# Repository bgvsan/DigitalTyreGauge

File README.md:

# DigitalTyreGauge
Digital tyre gauge

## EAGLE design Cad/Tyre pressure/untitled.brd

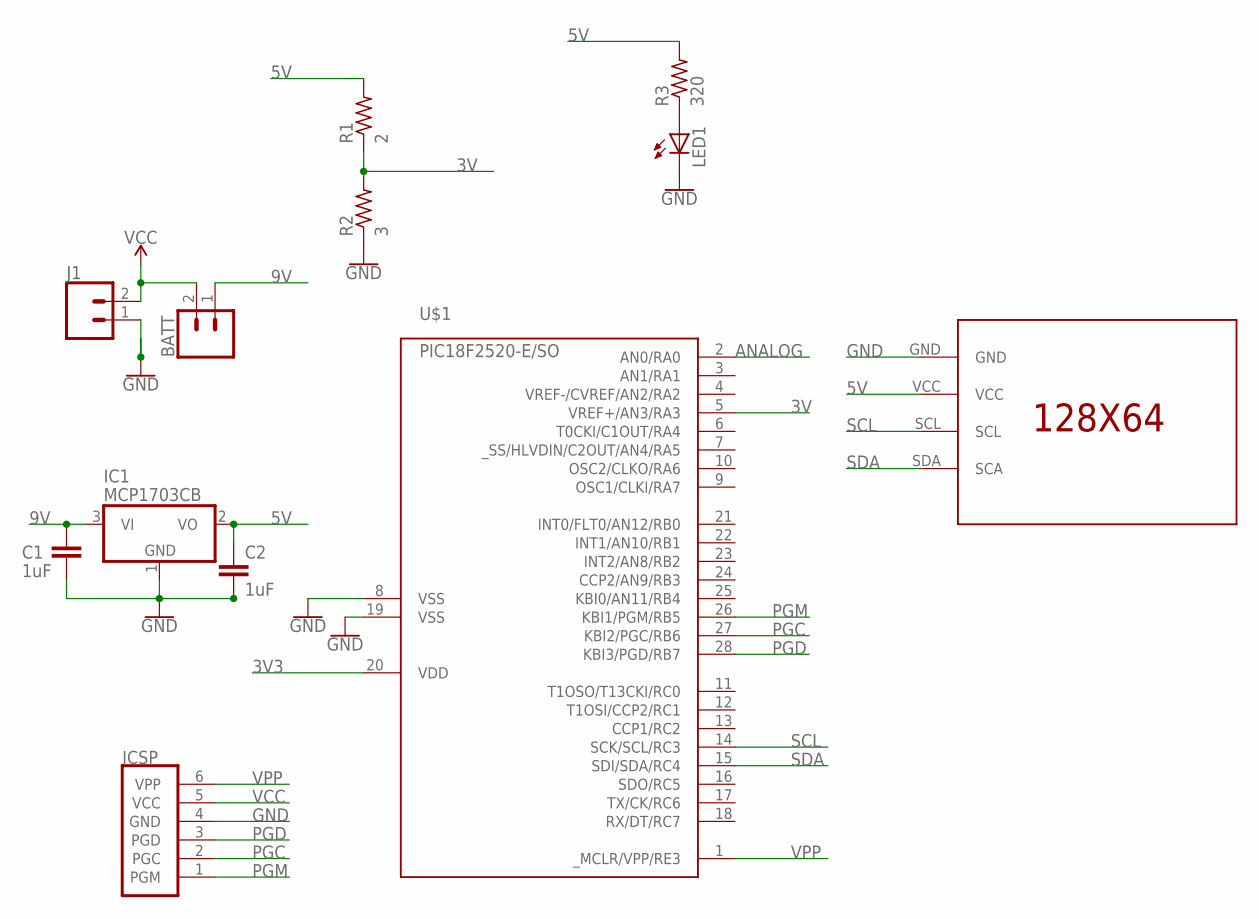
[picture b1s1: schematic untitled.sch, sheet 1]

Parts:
BATT: CONN_02; 1X02
C1, C2: 1uF; 0805
IC1: MCP1703CB; SOT23
ICSP: PIC_ICSP_6_PIN; MOLEX-1X6
J1: CONN_02; 1X02
LED1: LEDCHIP-LED0805; CHIP-LED0805
R1: 2; R0805
R2: 3; R0805
R3: 320; R0805
U$1: PIC18F2520-E/SO; SO-28W
U$2: 128_64_OLED_SPI

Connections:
3V: R1.1, R2.2, U$1.5 (VREF+/AN3/RA3)
3V3: U$1.20 (VDD)
5V: C2.1, IC1.2 (VO), R1.2, R3.2, U$2.VCC; also elsewhere on the board
9V: BATT.1, C1.1, IC1.3 (VI)
ANALOG: U$1.2 (AN0/RA0); also elsewhere on the board
GND: C1.2, C2.2, IC1.1 (GND), ICSP.4 (GND), J1.1, LED1.C, R2.1, U$1.8 (VSS), U$1.19 (VSS), U$2.GND; also elsewhere on the board
unnamed: LED1.A, R3.1
PGC: ICSP.2 (PGC), U$1.27 (KBI2/PGC/RB6)
PGD: ICSP.3 (PGD), U$1.28 (KBI3/PGD/RB7)
PGM: ICSP.1 (PGM), U$1.26 (KBI1/PGM/RB5)
SCL: U$1.14 (SCK/SCL/RC3), U$2.SCL
SDA: U$1.15 (SDI/SDA/RC4), U$2.SDA (SCA)
VCC: BATT.2, ICSP.5 (VCC), J1.2
VPP: ICSP.6 (VPP), U$1.1 (_MCLR/VPP/RE3)

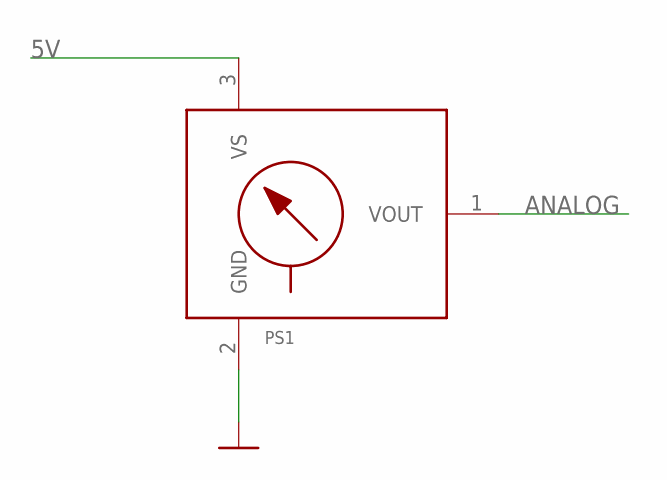
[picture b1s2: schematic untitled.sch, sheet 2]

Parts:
PS1: MPX-867B-H; 867B-H

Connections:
5V: PS1.3 (VS); also elsewhere on the board
ANALOG: PS1.1 (VOUT); also elsewhere on the board
GND: PS1.2 (GND); also elsewhere on the board

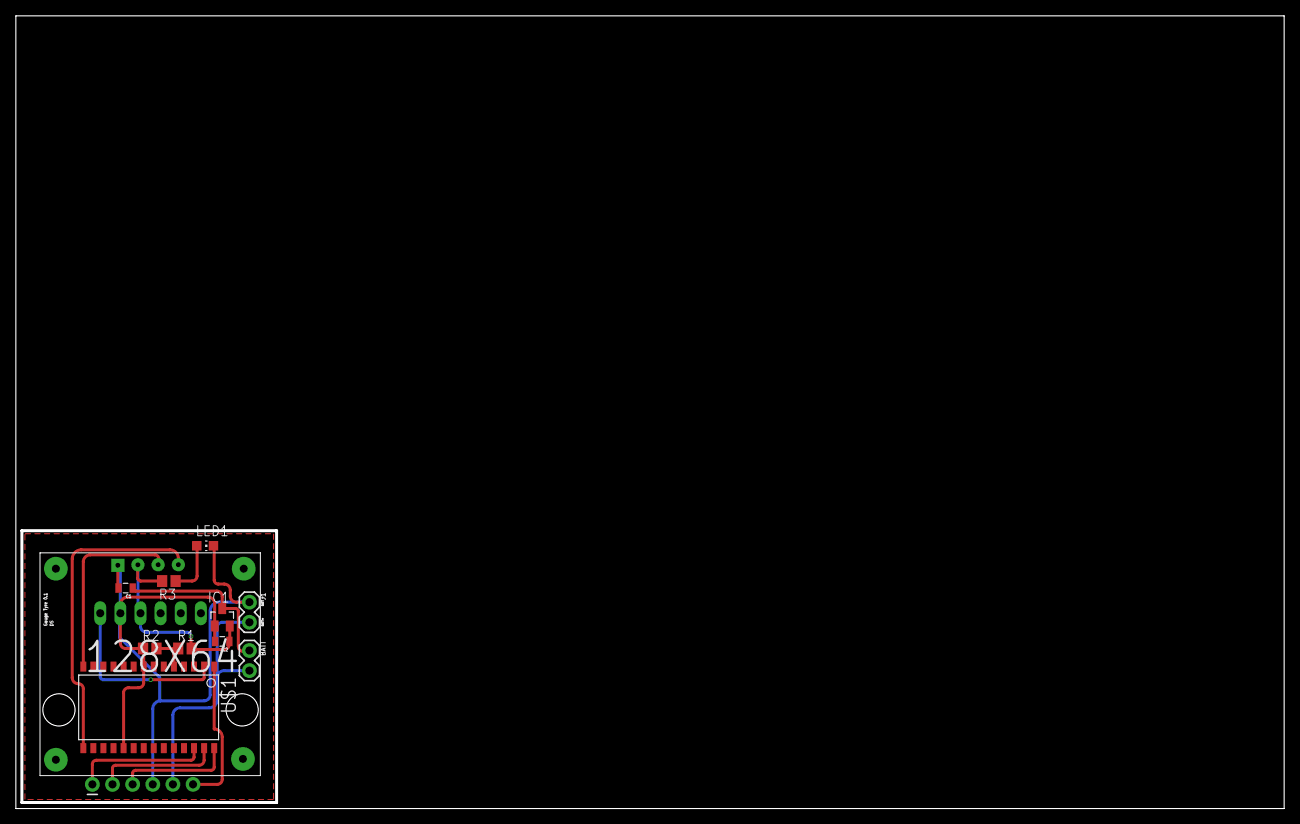
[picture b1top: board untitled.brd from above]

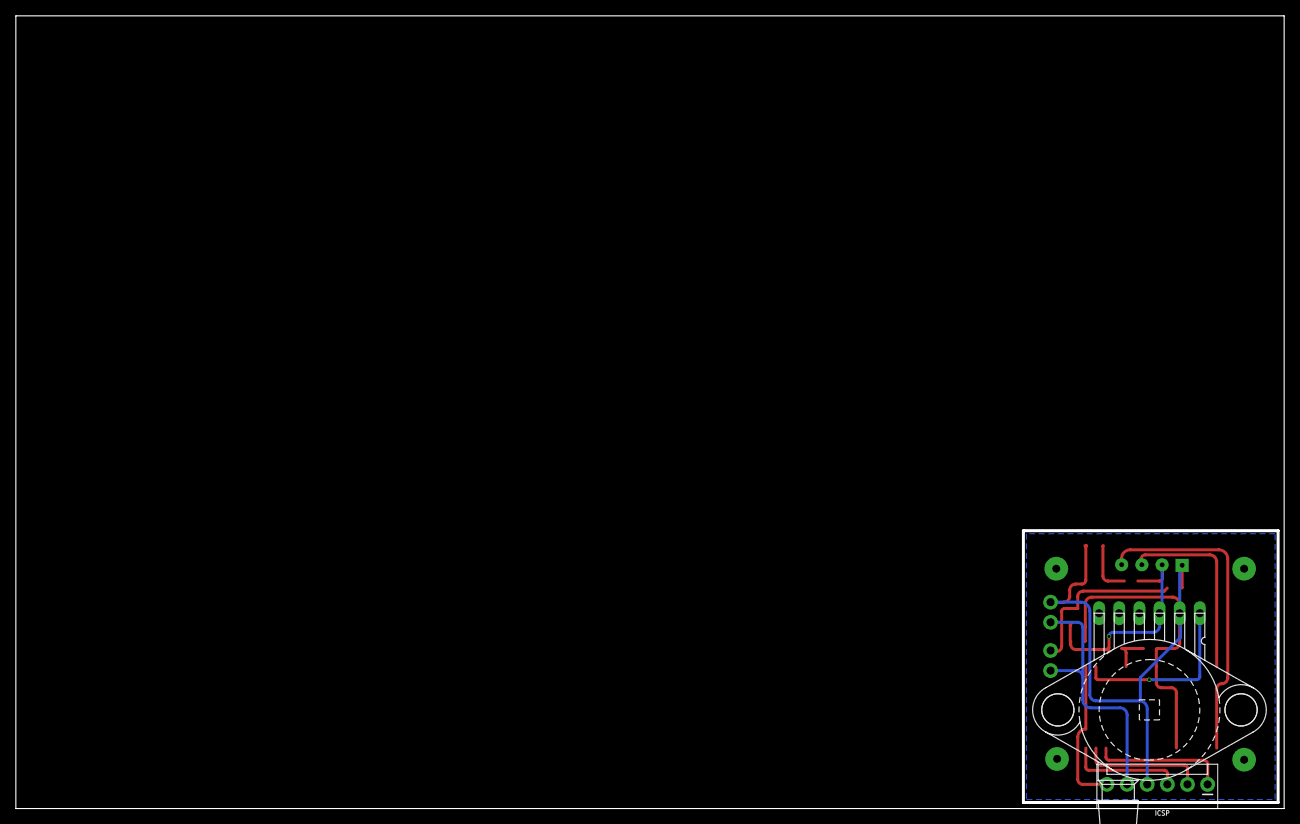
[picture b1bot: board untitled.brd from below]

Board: 2 copper layers, 160.0 x 100.0 mm, 13 parts (2 on the bottom side), 13 nets.

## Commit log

2019-05-30 mplax X project creation
    mplax X project creation
2019-05-30 added datasheet
2019-06-09 added datasheet and eagle file
2019-06-11 first Wiring stubb
    first Wiring stubb
2019-06-17 add adafruit ssd1306 lib
2019-06-17 add gerber
    Add gerber and layout to the board
2019-06-17 Update SuppressibleMessageMemo.properties
    Adding library
2019-06-17 add library
    Add oled library
    Added i2c lib
2019-06-18 Create oled library tidy up init

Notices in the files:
parts and their libraries:
SparkFun-Connectors: Licensing: Creative Commons ShareAlike 4.0 International - https://creativecommons.org/licenses/by-sa/4.0
